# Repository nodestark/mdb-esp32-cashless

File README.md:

<div align="center">

# VMflow — Open-Source Vending Machine IoT Platform

**The first open-source vending platform designed for AI agents.**
</div>

---

The project aims to provide a modern, open, and extensible platform for vending machine connectivity. Based on the ESP32 platform, it enables machines to communicate via Bluetooth and cloud services, receive remote credits, report telemetry, and integrate with mobile applications and web dashboards.

# Features
- ESP32-based vending machine controller implementing MDB telemetry, cashless payments, and IoT connectivity;
- PCB design done in **KiCad**, facilitating production and customization of the hardware;
- Support for **EVA DTS DEX/DDCMP** (European Vending Association Data Transfer Standard), allowing remote monitoring and control of machines;
- **Web Dashboard**: [📊 Open Dashboard](https://vmflow.xyz/dashboard) – Centralized interface to monitor the vending machine network in real time, including device status, telemetry, sales data, inventory control, product catalog management, and real-time stock alerts. Features AI-powered diagnostics (via OpenAI) for operation-wide analysis, per-machine insights, and product catalog recommendations;
- **PAX Counter**: detects nearby mobile devices and periodically reports anonymized presence metrics to estimate foot traffic around the vending machine. This enables heatmaps, peak-hour analysis, and location performance insights;

# 🤖 Manage It With Your AI Agent

VMflow is built to be driven by AI agents — send credits, check device health, query sales, and trigger OTA updates, all from natural language.

**OpenClaw** — install the official VMflow skill:
```
$ openclaw skills install @nodestark/vmflow
```

**Any coding agent with a shell** (Claude Code, Codex, etc.) — [vmflow-cli](https://github.com/nodestark/vmflow-cli), browser login, no tokens to copy/paste:
```bash
npm install -g vmflow-cli
vmflow-cli auth login
vmflow-cli device credit 51 1.50   # everything else: vmflow-cli --help
```

**Agents without shell access** (ChatGPT, browser-based assistants) — paste this and it picks up the whole API surface:
```
read https://raw.githubusercontent.com/nodestark/mdb-esp32-cashless/main/AGENTS.md
```

# Getting Started

### 1. Flash the Firmware

👉 Install firmware via Web Installer (no setup required): **https://install.vmflow.xyz**

👉 Advanced (for development): ESP-IDF

```bash
# Clone the repository (with submodules — pulls in the VMC project)
git clone --recurse-submodules https://github.com/nodestark/mdb-esp32-cashless
cd mdb-esp32-cashless/mdb-slave-esp32s3

idf.py flash monitor
```
### 2. Register and Configure the Device — VMflow [Android App](./android)

Use the **VMflow Android app** to register the board and link it to your operator account. The app allows you to:

- **Device Registration**: register telemetry boards and bind them to your operator account
- **Wi-Fi Configuration**: remotely configure the Wi-Fi network of your devices via Bluetooth
- **Send Credits**: interact with devices in real time via Bluetooth and MQTT

## Hardware

---

### 1️⃣ Get a Bearer Token

```bash
curl -X POST 'https://supabase.vmflow.xyz/auth/v1/token?grant_type=password' \
-H "apikey: eyJhbGciOiJIUzI1NiIsInR5cCI6IkpXVCJ9.eyJyb2xlIjoiYW5vbiIsImlzcyI6InN1cGFiYXNlLWRlbW8iLCJpYXQiOjE2NDE3NjkyMDAsImV4cCI6MTc5OTUzNTYwMH0.VGEEIztVo-do9cy_Qw2-2sF8bSONckhX71Nvtwj15X4" \
-H "Content-Type: application/json" \
-d '{ "email": "your_email@domain.xyz", "password": "your_password"}'
```

### 2️⃣ Send Credit to the Machine over MQTT

```bash
curl -X POST 'https://supabase.vmflow.xyz/functions/v1/send-credit' \
-H "apikey: eyJhbGciOiJIUzI1NiIsInR5cCI6IkpXVCJ9.eyJyb2xlIjoiYW5vbiIsImlzcyI6InN1cGFiYXNlLWRlbW8iLCJpYXQiOjE2NDE3NjkyMDAsImV4cCI6MTc5OTUzNTYwMH0.VGEEIztVo-do9cy_Qw2-2sF8bSONckhX71Nvtwj15X4" \
-H "Authorization: Bearer YOUR_ACCESS_TOKEN" \
-H "Content-Type: application/json" \
-d '{ "subdomain":51,"amount":1.50 }'
```

### 💸 Pay with x402 (crypto / AI agents)

[x402](https://x402.org) lets a person or an AI agent pay a machine directly over HTTP — no checkout page, no webhook. Call without payment to get a 402 quote, retry with a signed `X-PAYMENT` header to vend. Operator setup: add a `credentials` row with key `x402_pay_to` and your receiving wallet address.

```bash
# 1. Get a quote (returns 402 + payment requirements)
curl -X POST 'https://supabase.vmflow.xyz/functions/v1/x402-vend' \
-H "apikey: eyJhbGciOiJIUzI1NiIsInR5cCI6IkpXVCJ9.eyJyb2xlIjoiYW5vbiIsImlzcyI6InN1cGFiYXNlLWRlbW8iLCJpYXQiOjE2NDE3NjkyMDAsImV4cCI6MTc5OTUzNTYwMH0.VGEEIztVo-do9cy_Qw2-2sF8bSONckhX71Nvtwj15X4" \
-H "Content-Type: application/json" \
-d '{ "subdomain":51,"amount":1.50 }'

# 2. Retry with the signed payment (any x402 client library builds this header)
curl -X POST 'https://supabase.vmflow.xyz/functions/v1/x402-vend' \
-H "apikey: eyJhbGciOiJIUzI1NiIsInR5cCI6IkpXVCJ9.eyJyb2xlIjoiYW5vbiIsImlzcyI6InN1cGFiYXNlLWRlbW8iLCJpYXQiOjE2NDE3NjkyMDAsImV4cCI6MTc5OTUzNTYwMH0.VGEEIztVo-do9cy_Qw2-2sF8bSONckhX71Nvtwj15X4" \
-H "X-PAYMENT: <base64 payment payload>" \
-H "Content-Type: application/json" \
-d '{ "subdomain":51,"amount":1.50 }'
```

**Operator payouts:** [vmflow-spraay](https://github.com/plagtech/vmflow-spraay) — automated multi-party revenue splits for VMflow sales, settled as one batch transaction on Base (non-custodial, MIT).

### 3️⃣ View Sales

```bash
curl -X GET 'https://supabase.vmflow.xyz/rest/v1/sales' \
-H "apikey: eyJhbGciOiJIUzI1NiIsInR5cCI6IkpXVCJ9.eyJyb2xlIjoiYW5vbiIsImlzcyI6InN1cGFiYXNlLWRlbW8iLCJpYXQiOjE2NDE3NjkyMDAsImV4cCI6MTc5OTUzNTYwMH0.VGEEIztVo-do9cy_Qw2-2sF8bSONckhX71Nvtwj15X4" \
-H "Authorization: Bearer YOUR_ACCESS_TOKEN"
```

### 4️⃣ View Devices

```bash
curl -X GET 'https://supabase.vmflow.xyz/rest/v1/embedded' \
-H "apikey: eyJhbGciOiJIUzI1NiIsInR5cCI6IkpXVCJ9.eyJyb2xlIjoiYW5vbiIsImlzcyI6InN1cGFiYXNlLWRlbW8iLCJpYXQiOjE2NDE3NjkyMDAsImV4cCI6MTc5OTUzNTYwMH0.VGEEIztVo-do9cy_Qw2-2sF8bSONckhX71Nvtwj15X4" \
-H "Authorization: Bearer YOUR_ACCESS_TOKEN"
```

### 5️⃣ View Paxcounter

```bash
curl -X GET 'https://supabase.vmflow.xyz/rest/v1/metrics?name=eq.paxcounter' \
-H "apikey: eyJhbGciOiJIUzI1NiIsInR5cCI6IkpXVCJ9.eyJyb2xlIjoiYW5vbiIsImlzcyI6InN1cGFiYXNlLWRlbW8iLCJpYXQiOjE2NDE3NjkyMDAsImV4cCI6MTc5OTUzNTYwMH0.VGEEIztVo-do9cy_Qw2-2sF8bSONckhX71Nvtwj15X4" \
-H "Authorization: Bearer YOUR_ACCESS_TOKEN"
```

# How to Contribute:
- Contributions are welcome! Feel free to open issues, send pull requests, or propose new features
- Before submitting a pull request, make sure the code complies with the style and quality guidelines defined in the project
- Help us improve documentation by adding usage examples, installation instructions, and any other relevant information

## License

This project is licensed under the MIT License - see the [LICENSE](LICENSE) file for details.

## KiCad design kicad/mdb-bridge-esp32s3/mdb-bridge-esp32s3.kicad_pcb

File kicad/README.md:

# MDB ESP32 Cashless Devices

This repository contains open hardware projects for MDB-based cashless devices built around the ESP32 platform.

## PCBWay Project Store
You can view and order the PCBs directly from PCBWay using the link below:

👉 https://www.pcbway.com/project/member/?bmbno=1B3B95CB-4E28-4D

---

### MDB ESP32 Cashless Device

[Schematic (PDF)](schematic-mdb-slave-esp32s3.pdf)

### MDB ESP32 GPS/LTE-M/NB-IoT Cashless Device

[Schematic (PDF)](schematic-mdb-slave-esp32s3-sim7080g.pdf)

### MDB ESP32 Cashless Device (Mini, 0402)

[Schematic (PDF)](schematic-mdb-slave-esp32s3-mini.pdf)

### MDB ESP32 Cashless/VMC Device

[Schematic (PDF)](schematic-mdb-bridge-esp32s3.pdf)

Two independent MDB ports: the board is the master on the **controller** port (peripherals: coin changer, bill validator) and a slave on the **target** port (the vending machine's VMC).

| Port           | RX  | TX  | Board role         | Connects to                               |
|----------------|-----|-----|--------------------|-------------------------------------------|
| **Controller** | IO1 | IO2 | master (VMC)       | peripherals: coin changer, bill validator |
| **Target**     | IO4 | IO5 | slave (peripheral) | the vending machine's VMC/master          |

### MDB ESP32 AI Bridge (VMflow + VMC + Bill/Coin Reader simulator)
Three ESP32-S3 on one board, each simulating one role of the vending stack — VMflow cashless device, VMC and bill/coin reader — linked by logic-level MDB and reachable through a single USB-C via a USB2514B hub. Bench/CI target for firmware and AI agents without a vending machine.

[Schematic (PDF)](schematic-mdb-ai-bridge-esp32s3.pdf)

The bridge MCU keeps the pinout of the MDB ESP32 Cashless/VMC Device, so the same firmware runs on both boards; the two simulators sit on its ports in place of the real peripherals and VMC.

| MCU    | Role                               | MDB RX | MDB TX | USB hub port |
|--------|------------------------------------|--------|--------|--------------|
| **U5** | VMflow bridge, controller port     | IO1    | IO2    | 2            |
| **U5** | VMflow bridge, target port         | IO4    | IO5    | 2            |
| **U2** | bill/coin reader simulator (slave) | IO4    | IO5    | 1            |
| **U1** | VMC simulator (master)             | IO1    | IO2    | 3            |

The bridge also reaches the VMC simulator's UART0 console (bridge IO8 ← U0TXD, IO9 → U0RXD). I²C (SDA IO10, SCL IO11) is shared by all three, with 4.7k pull-ups. The J3 2×8 header exposes both MDB links, the I²C bus and bridge IO12–IO14, IO17 and IO18.

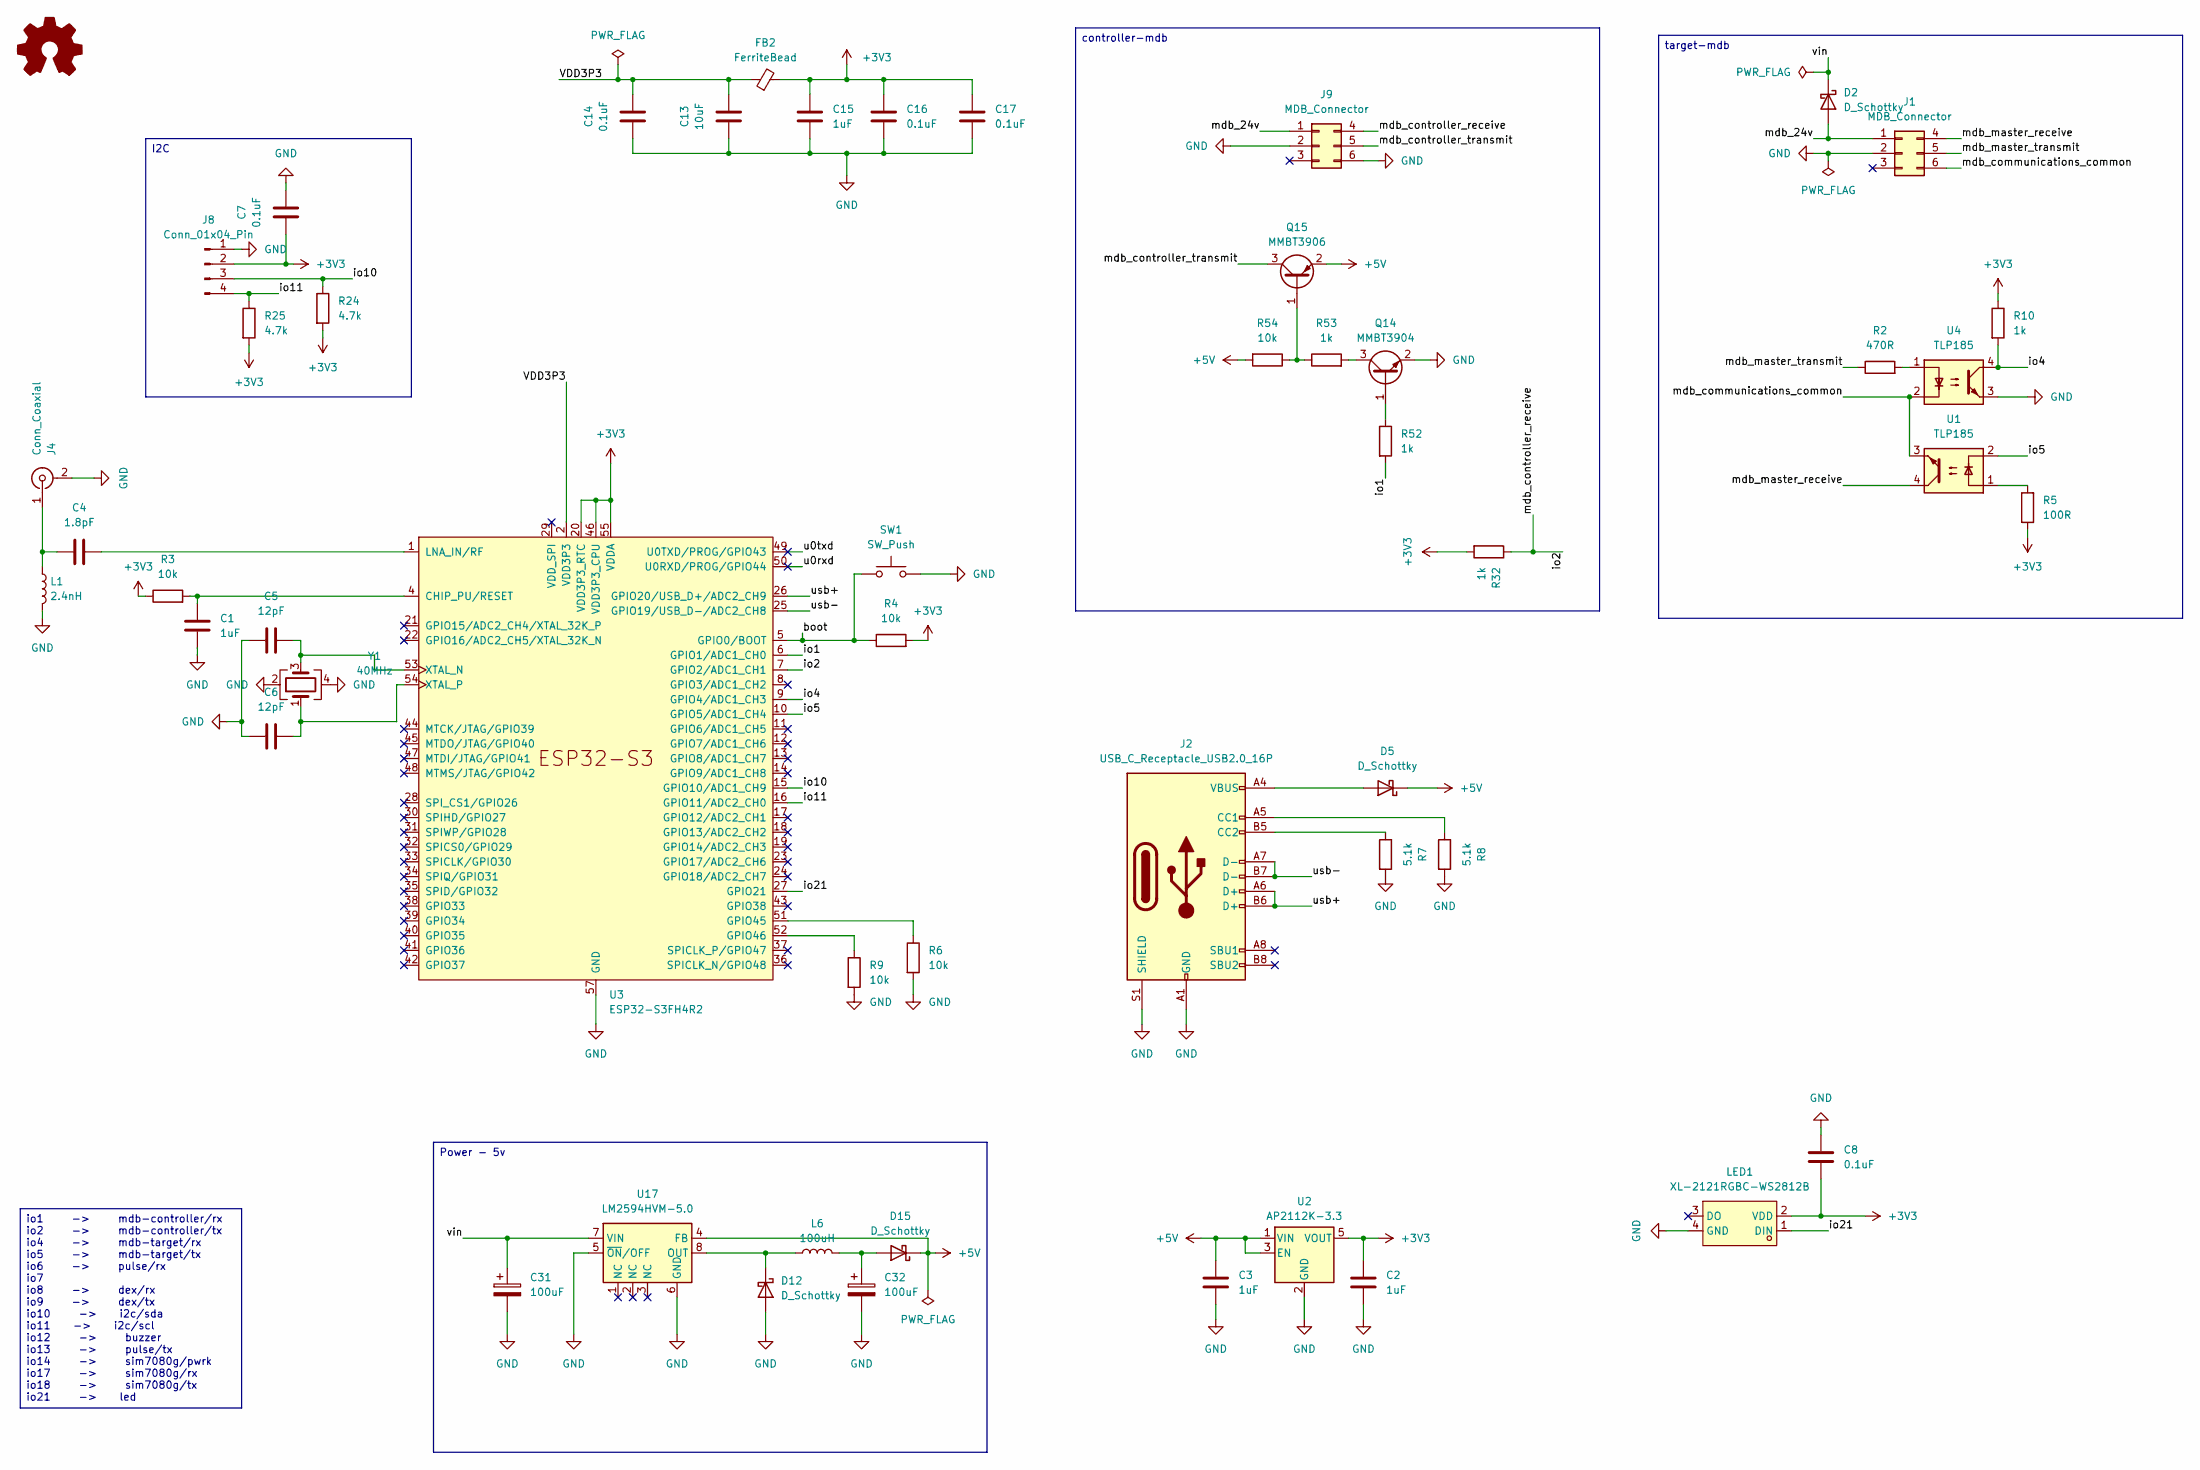
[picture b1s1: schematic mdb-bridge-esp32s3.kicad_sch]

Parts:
C1, C2, C3, C15: 1uF; C_0603_1608Metric; LCSC# C696901
C4: 1.8pF; C_0603_1608Metric; LCSC# C376773
C5, C6: 12pF; C_0603_1608Metric; LCSC# C363546
C7, C8, C14, C16, C17: 0.1uF; C_0603_1608Metric; LCSC# C5137636
C13: 10uF; C_0603_1608Metric; LCSC# C6119864
C31: 100uF; CP_Elec_6.3x5.8; LCSC# C128464
C32: 100uF; CP_EIA-3528-21_Kemet-B; LCSC# C90975
D2, D5, D12, D15: D_Schottky; D_SOD-123; LCSC# C18195164
FB2: FerriteBead; L_0603_1608Metric; LCSC# C14709
J1, J9: MDB_Connector; Molex_Mini-Fit_Jr_5566-06A_2x03_P4.20mm_Vertical; LCSC# C22365701
J2: USB_C_Receptacle_USB2.0_16P; USB_C_Receptacle_G-Switch_GT-USB-7010ASV; LCSC# C2988369
J4: Conn_Coaxial; U.FL_Hirose_U.FL-R-SMT-1_Vertical; LCSC# C88374
J8: Conn_01x04_Pin; JST_PH_B4B-PH-K_1x04_P2.00mm_Vertical; LCSC# C131334
L1: 2.4nH; L_0603_1608Metric; LCSC# C2042508
L6: 100uH; L_7.3x7.3_H3.5; LCSC# C182195
LED1: XL-2121RGBC-WS2812B; LED-SMD_4P-L2.1-W2.1-BR_XL-2121RGBC-WS2812B; MPN XL-2121RGBC-2812B; LCSC# C5349957
Q14: MMBT3904; SOT-23; LCSC# C916374
Q15: MMBT3906; SOT-23; LCSC# C364311
R2: 470R; R_0603_1608Metric; LCSC# C114669
R3, R4, R6, R9, R54: 10k; R_0603_1608Metric; LCSC# C98220
R5: 100R; R_0603_1608Metric; LCSC# C22775
R7, R8: 5.1k; R_0603_1608Metric; LCSC# C394543
R10, R32, R52, R53: 1k; R_0603_1608Metric; LCSC# C2907113
R24, R25: 4.7k; R_0603_1608Metric; LCSC# C23162
SW1: SW_Push; SW_Tactile_SPST_NO_Straight_CK_PTS636Sx25SMTRLFS; LCSC# C42435421
U1, U4: TLP185; SOP-4_3.8x4.1mm_P2.54mm; LCSC# C128776
U2: AP2112K-3.3; SOT-23-5; LCSC# C51118
U3: ESP32-S3FH4R2; QFN-56-1EP_7x7mm_P0.4mm_EP4x4mm; LCSC# C3013940
U17: LM2594HVM-5.0; SOIC-8_3.9x4.9mm_P1.27mm; LCSC# C2904794
Y1: 40MHz; Crystal_SMD_3225-4Pin_3.2x2.5mm; LCSC# C7294599

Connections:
+3V3: C2.2, C7.1, C8.2, C15.2, C16.1, C17.1, FB2.2, J8.2, LED1.2 (VDD), R3.1, R4.2, R5.1, R10.1, R24.2, R25.2, R32.2, U2.5 (VOUT), U3.20 (VDD3P3_RTC), U3.46 (VDD3P3_CPU), U3.55 (VDDA), U3.56 (VDDA)
+5V: C3.2, D5.1 (K), D15.1 (K), Q15.2 (E), R54.2, U2.1 (VIN), U2.3 (EN), U17.4 (FB)
/boot: R4.1, SW1.1, U3.5 (GPIO0/BOOT)
/io1: R52.2, U3.6 (GPIO1/ADC1_CH0)
/io2: J9.4, R32.1, U3.7 (GPIO2/ADC1_CH1)
/io4: R10.2, U3.9 (GPIO4/ADC1_CH3), U4.4
/io5: U1.2, U3.10 (GPIO5/ADC1_CH4)
/io10: J8.3, R24.1, U3.15 (GPIO10/ADC1_CH9)
/io11: J8.4, R25.1, U3.16 (GPIO11/ADC2_CH0)
/io21: LED1.1 (DIN), U3.27 (GPIO21)
/mdb_24v: D2.2 (A), J1.1, J9.1
/mdb_communications_common: J1.6, U1.3, U4.2
/mdb_controller_transmit: J9.5, Q15.3 (C)
/mdb_master_receive: J1.4, U1.4
/mdb_master_transmit: J1.5, R2.1
/u0rxd: U3.50 (U0RXD/PROG/GPIO44)
/u0txd: U3.49 (U0TXD/PROG/GPIO43)
/usb+: J2.A6 (D+), J2.B6 (D+), U3.26 (GPIO20/USB_D+/ADC2_CH9)
/usb-: J2.A7 (D-), J2.B7 (D-), U3.25 (GPIO19/USB_D-/ADC2_CH8)
/vin: C31.1, D2.1 (K), U17.7 (VIN)
GND: C1.2, C2.1, C3.1, C5.1, C6.1, C7.2, C8.1, C13.1, C14.1, C15.1, C16.2, C17.2, C31.2, C32.2, D12.2 (A), J1.2, J2.A1 (GND), J2.A12 (GND), J2.B1 (GND), J2.B12 (GND), J2.S1 (SHIELD), J4.2 (Ext), J8.1, J9.2, J9.6, L1.2, LED1.4 (GND), Q14.2 (E), R6.2, R7.2, R8.2, R9.2, SW1.2, U2.2 (GND), U3.57 (GND), U4.3, U17.5 (~ON/OFF), U17.6 (GND), Y1.2, Y1.4
unnamed: D5.2 (A), J2.A4 (VBUS), J2.A9 (VBUS), J2.B4 (VBUS), J2.B9 (VBUS)
unnamed: D12.1 (K), L6.1, U17.8 (OUT)
unnamed: C32.1, D15.2 (A), L6.2
unnamed: J2.A5 (CC1), R8.1
unnamed: J2.B5 (CC2), R7.1
unnamed: C4.1, J4.1 (In), L1.1
unnamed: Q14.1 (B), R52.1
unnamed: Q14.3 (C), R53.2
unnamed: Q15.1 (B), R53.1, R54.1
unnamed: R2.2, U4.1
unnamed: R5.2, U1.1
unnamed: C1.1, R3.2, U3.4 (CHIP_PU/RESET)
unnamed: R6.1, U3.51 (GPIO45)
unnamed: R9.1, U3.52 (GPIO46)
unnamed: C4.2, U3.1 (LNA_IN/RF)
unnamed: C5.2, U3.53 (XTAL_N), Y1.3
unnamed: C6.2, U3.54 (XTAL_P), Y1.1
VDD3P3: C13.2, C14.2, FB2.1, U3.2 (VDD3P3), U3.3 (VDD3P3)

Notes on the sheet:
io1 -> mdb-controller/rx io2 -> mdb-controller/tx io4 -> mdb-target/rx io5 -> mdb-target/tx io6 -> pulse/rx io7 io8 -> dex/rx io9 -> dex/tx io10 -> i2c/sda io11 -> i2c/scl io12 -> buzzer io13 -> pulse/tx io14 -> sim7080g/pwrk io17 -> sim7080g/rx io18 -> sim7080g/tx io21 -> led
controller-mdb
Power - 5v
target-mdb
I2C

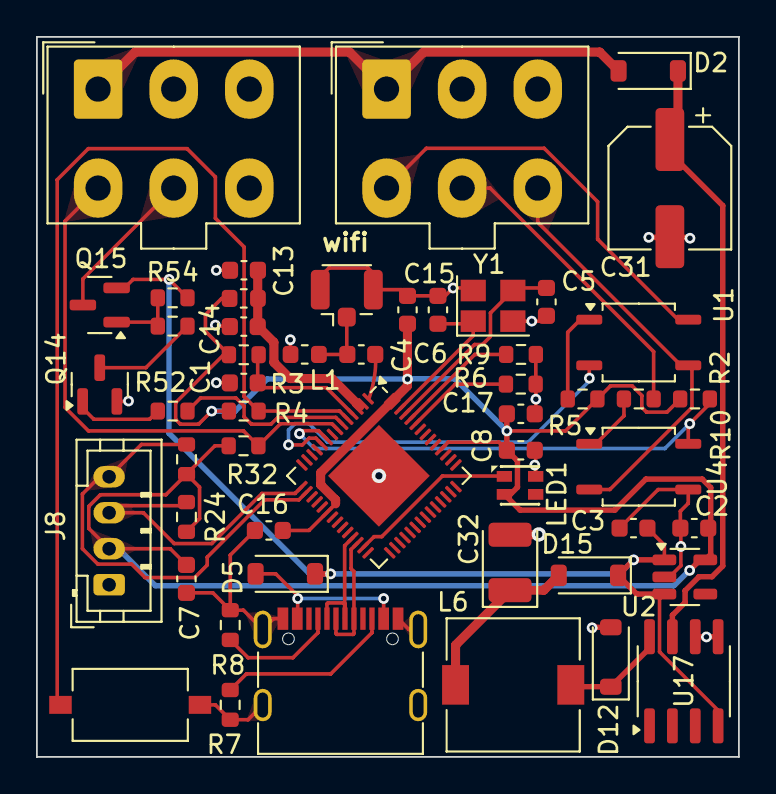
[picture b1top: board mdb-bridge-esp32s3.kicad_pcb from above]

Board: 2 copper layers, 39.0 x 40.0 mm, 52 parts (0 on the bottom side), 37 nets.

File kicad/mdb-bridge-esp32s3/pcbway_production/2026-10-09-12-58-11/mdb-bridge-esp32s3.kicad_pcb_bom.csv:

Designator,Quantity,Value,Footprint,Package,MPN,DNP,Mount_Type,LCSC#,Description,Manufacturer,Sim.Device,Sim.Pins
"C1, C15, C2, C3",4,1uF,C_0603_1608Metric,,,,smt,C696901,,,,
C13,1,10uF,C_0603_1608Metric,,,,smt,C6119864,,,,
"C14, C16, C17, C7, C8",5,0.1uF,C_0603_1608Metric,,,,smt,C5137636,,,,
C31,1,100uF,CP_Elec_6.3x5.8,,,,smt,C128464,Polarized capacitor,,,
C32,1,100uF,CP_EIA-3528-21_Kemet-B,,,,smt,C90975,Polarized capacitor,,,
C4,1,1.8pF,C_0603_1608Metric,,,,smt,C376773,,,,
"C5, C6",2,12pF,C_0603_1608Metric,,,,smt,C363546,,,,
"D12, D15, D2, D5",4,D_Schottky,D_SOD-123,,,,smt,C18195164,Schottky diode,,,
FB2,1,FerriteBead,L_0603_1608Metric,,,,smt,C14709,"Ferrite bead, small symbol",,,
"J1, J9",2,MDB_Connector,Molex_Mini-Fit_Jr_5566-06A_2x03_P4.20mm_Vertical,,,,tht,C22365701,"Generic connector, double row, 02x03, top/bottom pin numbering scheme (row 1: 1...pins_per_row, row2: pins_per_row+1 ... num_pins), script generated (kicad-library-utils/schlib/autogen/connector/)",,,
J2,1,USB_C_Receptacle_USB2.0_16P,USB_C_Receptacle_G-Switch_GT-USB-7010ASV,,,,smt,C2988369,USB 2.0-only 16P Type-C Receptacle connector,,,
J4,1,Conn_Coaxial,U.FL_Hirose_U.FL-R-SMT-1_Vertical,,,,smt,C88374,"coaxial connector (BNC, SMA, SMB, SMC, Cinch/RCA, LEMO, ...)",,,
J8,1,Conn_01x04_Pin,JST_PH_B4B-PH-K_1x04_P2.00mm_Vertical,,,,tht,C131334,"Generic connector, single row, 01x04, script generated",,,
L1,1,2.4nH,L_0603_1608Metric,,,,smt,C2042508,,,,
L6,1,100uH,L_7.3x7.3_H3.5,,,,smt,C182195,Inductor,,,
LED1,1,XL-2121RGBC-WS2812B,LED-SMD_4P-L2.1-W2.1-BR_XL-2121RGBC-WS2812B,,XL-2121RGBC-2812B,,smt,C5349957,,XINGLIGHT(成兴光),,
Q5,1,MMBT3906,SOT-23,,,,smt,C364311,"-0.2A Ic, -40V Vce, Small Signal PNP Transistor, SOT-23",,PNP,1=B 2=E 3=C
"R1, R10, R32",3,1k,R_0603_1608Metric,,,,smt,C2907113,,,,
R2,1,470R,R_0603_1608Metric,,,,smt,C114669,Resistor,,,
R5,1,100R,R_0603_1608Metric,,,,smt,C22775,Resistor,,,
"R24, R25, R31",3,4.7k,R_0603_1608Metric,,,,smt,C23162,,,,
"R3, R4, R6, R9",4,10k,R_0603_1608Metric,,,,smt,C98220,,,,
"R7, R8",2,5.1k,R_0603_1608Metric,,,,smt,C394543,,,,
SW1,1,SW_Push,SW_Tactile_SPST_NO_Straight_CK_PTS636Sx25SMTRLFS,,,,smt,C42435421,,,,
"U1, U4",2,TLP785,SOP-4_3.8x4.1mm_P2.54mm,,,,smt,C128776,"DC Optocoupler, Vce 80V, CTR 50-200%, DIP4",,,
U17,1,LM2594HVM-5.0,SOIC-8_3.9x4.9mm_P1.27mm,,,,smt,C2904794,"5.0V, 0.5A SIMPLE SWITCHER® Step-Down Voltage Regulator, Maximum VIN 60V, SOIC-8",,,
U2,1,AP2112K-3.3,SOT-23-5,,,,smt,C51118,"600mA low dropout linear regulator, with enable pin, 3.8V-6V input voltage range, 3.3V fixed positive output, SOT-23-5",,,
U3,1,ESP32-S3FH4R2,QFN-56-1EP_7x7mm_P0.4mm_EP4x4mm,,,,smt,C3013940,,,,
Y1,1,40MHz,Crystal_SMD_3225-4Pin_3.2x2.5mm,,,,smt,C7294599,"Four pin crystal, GND on pins 2 and 4",,,

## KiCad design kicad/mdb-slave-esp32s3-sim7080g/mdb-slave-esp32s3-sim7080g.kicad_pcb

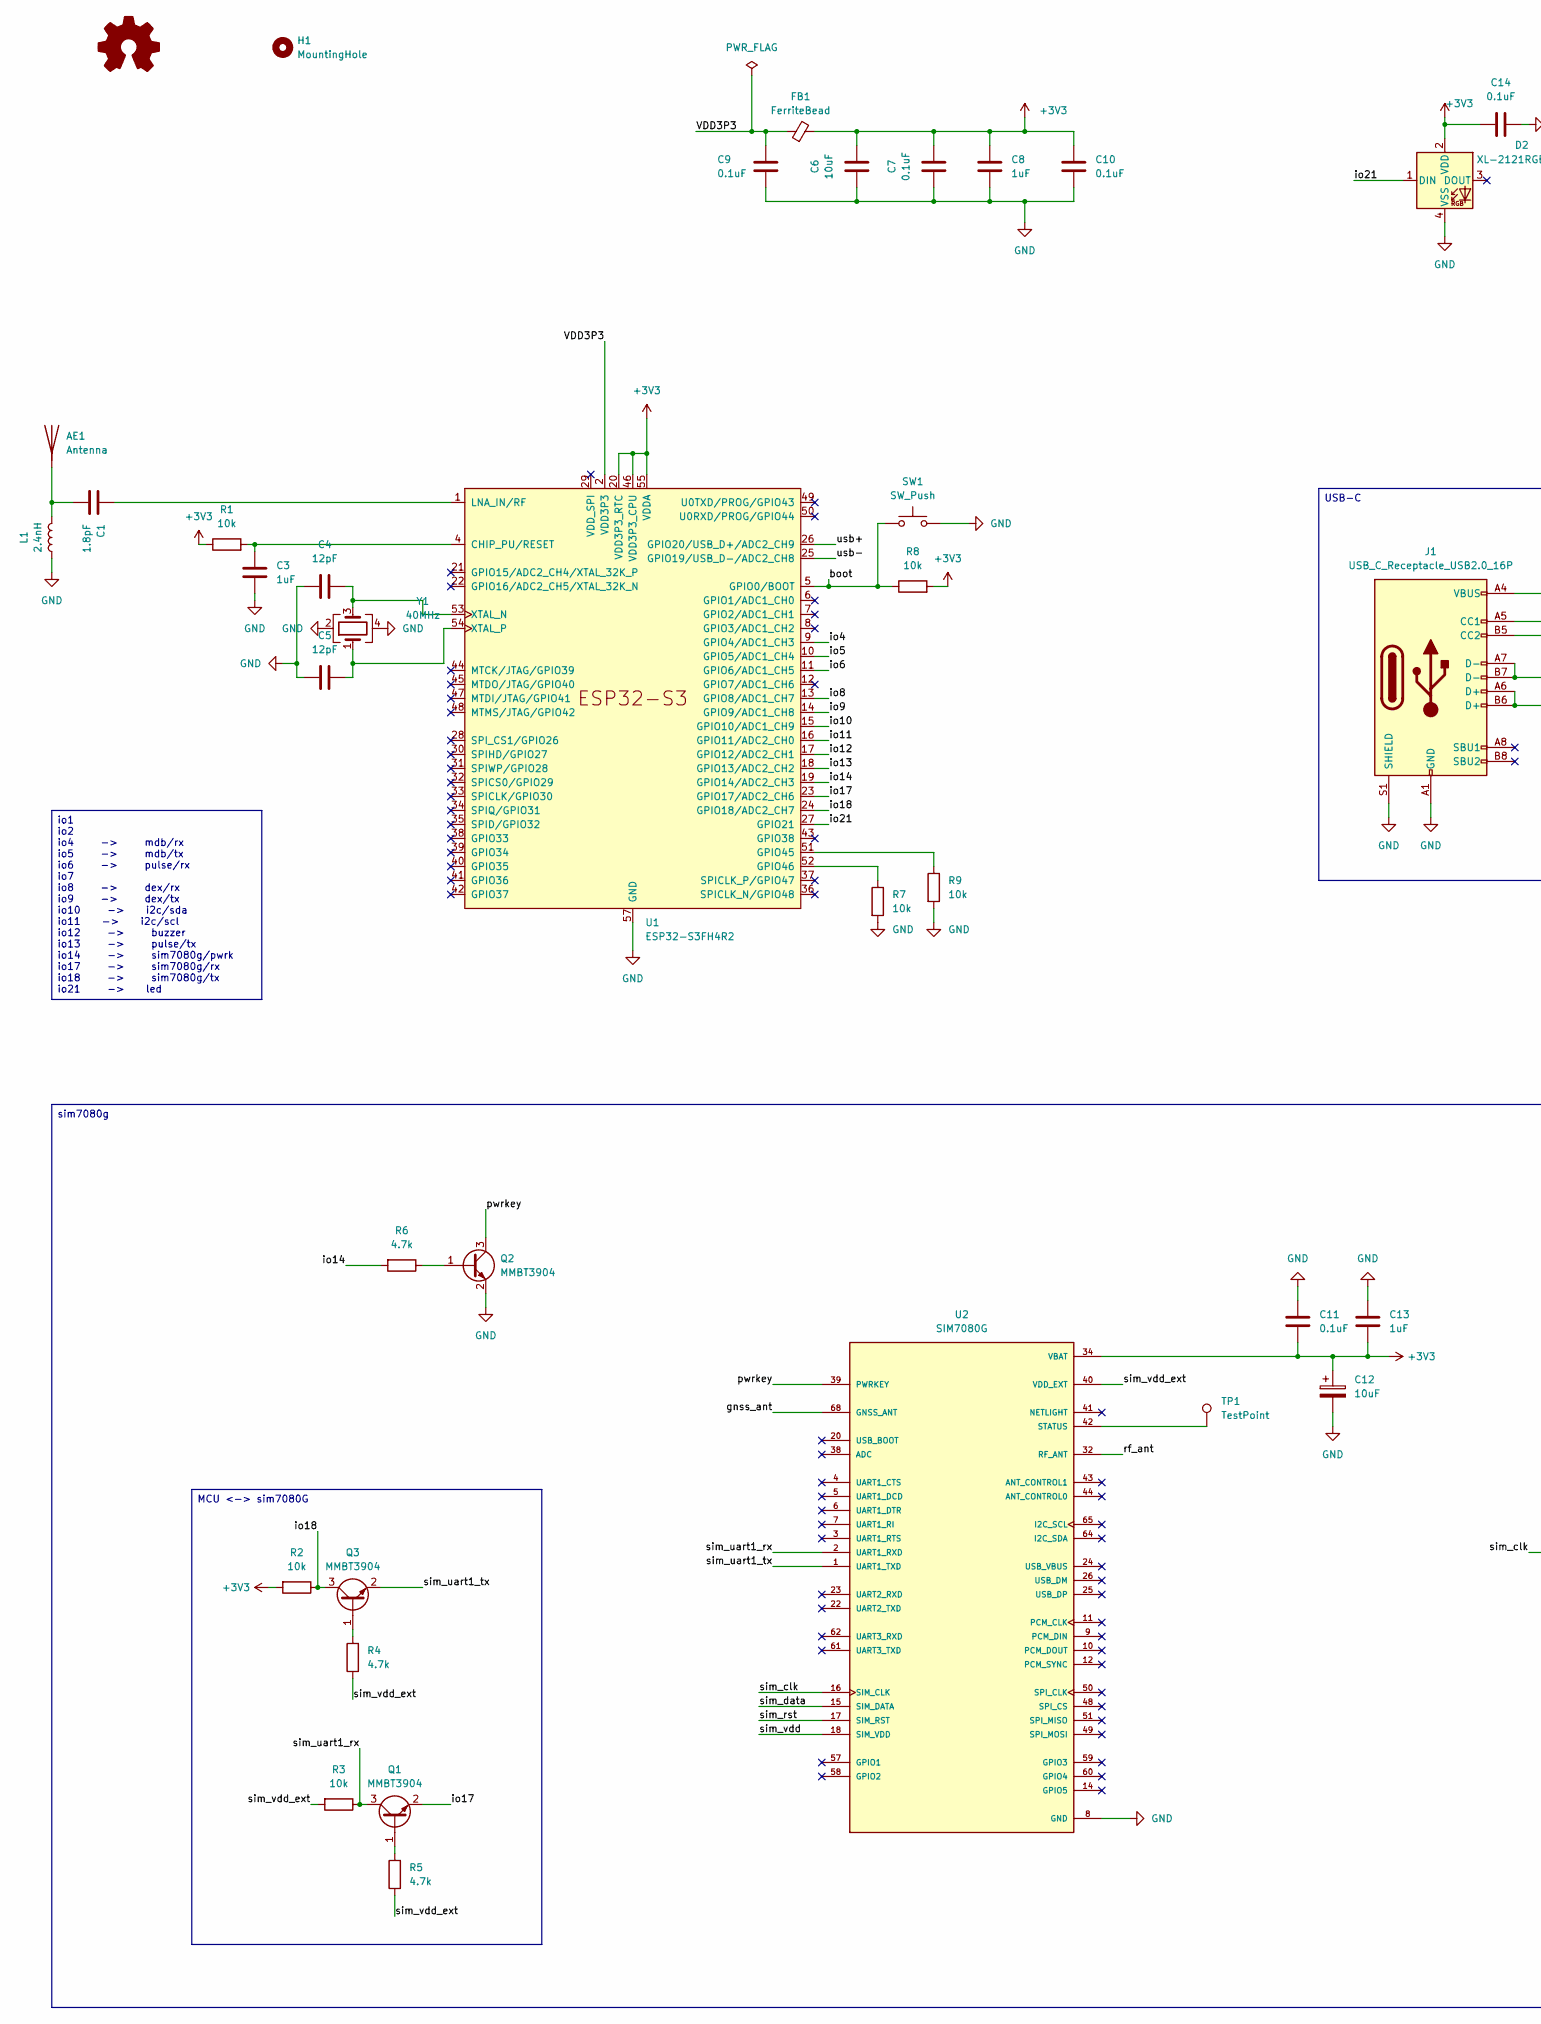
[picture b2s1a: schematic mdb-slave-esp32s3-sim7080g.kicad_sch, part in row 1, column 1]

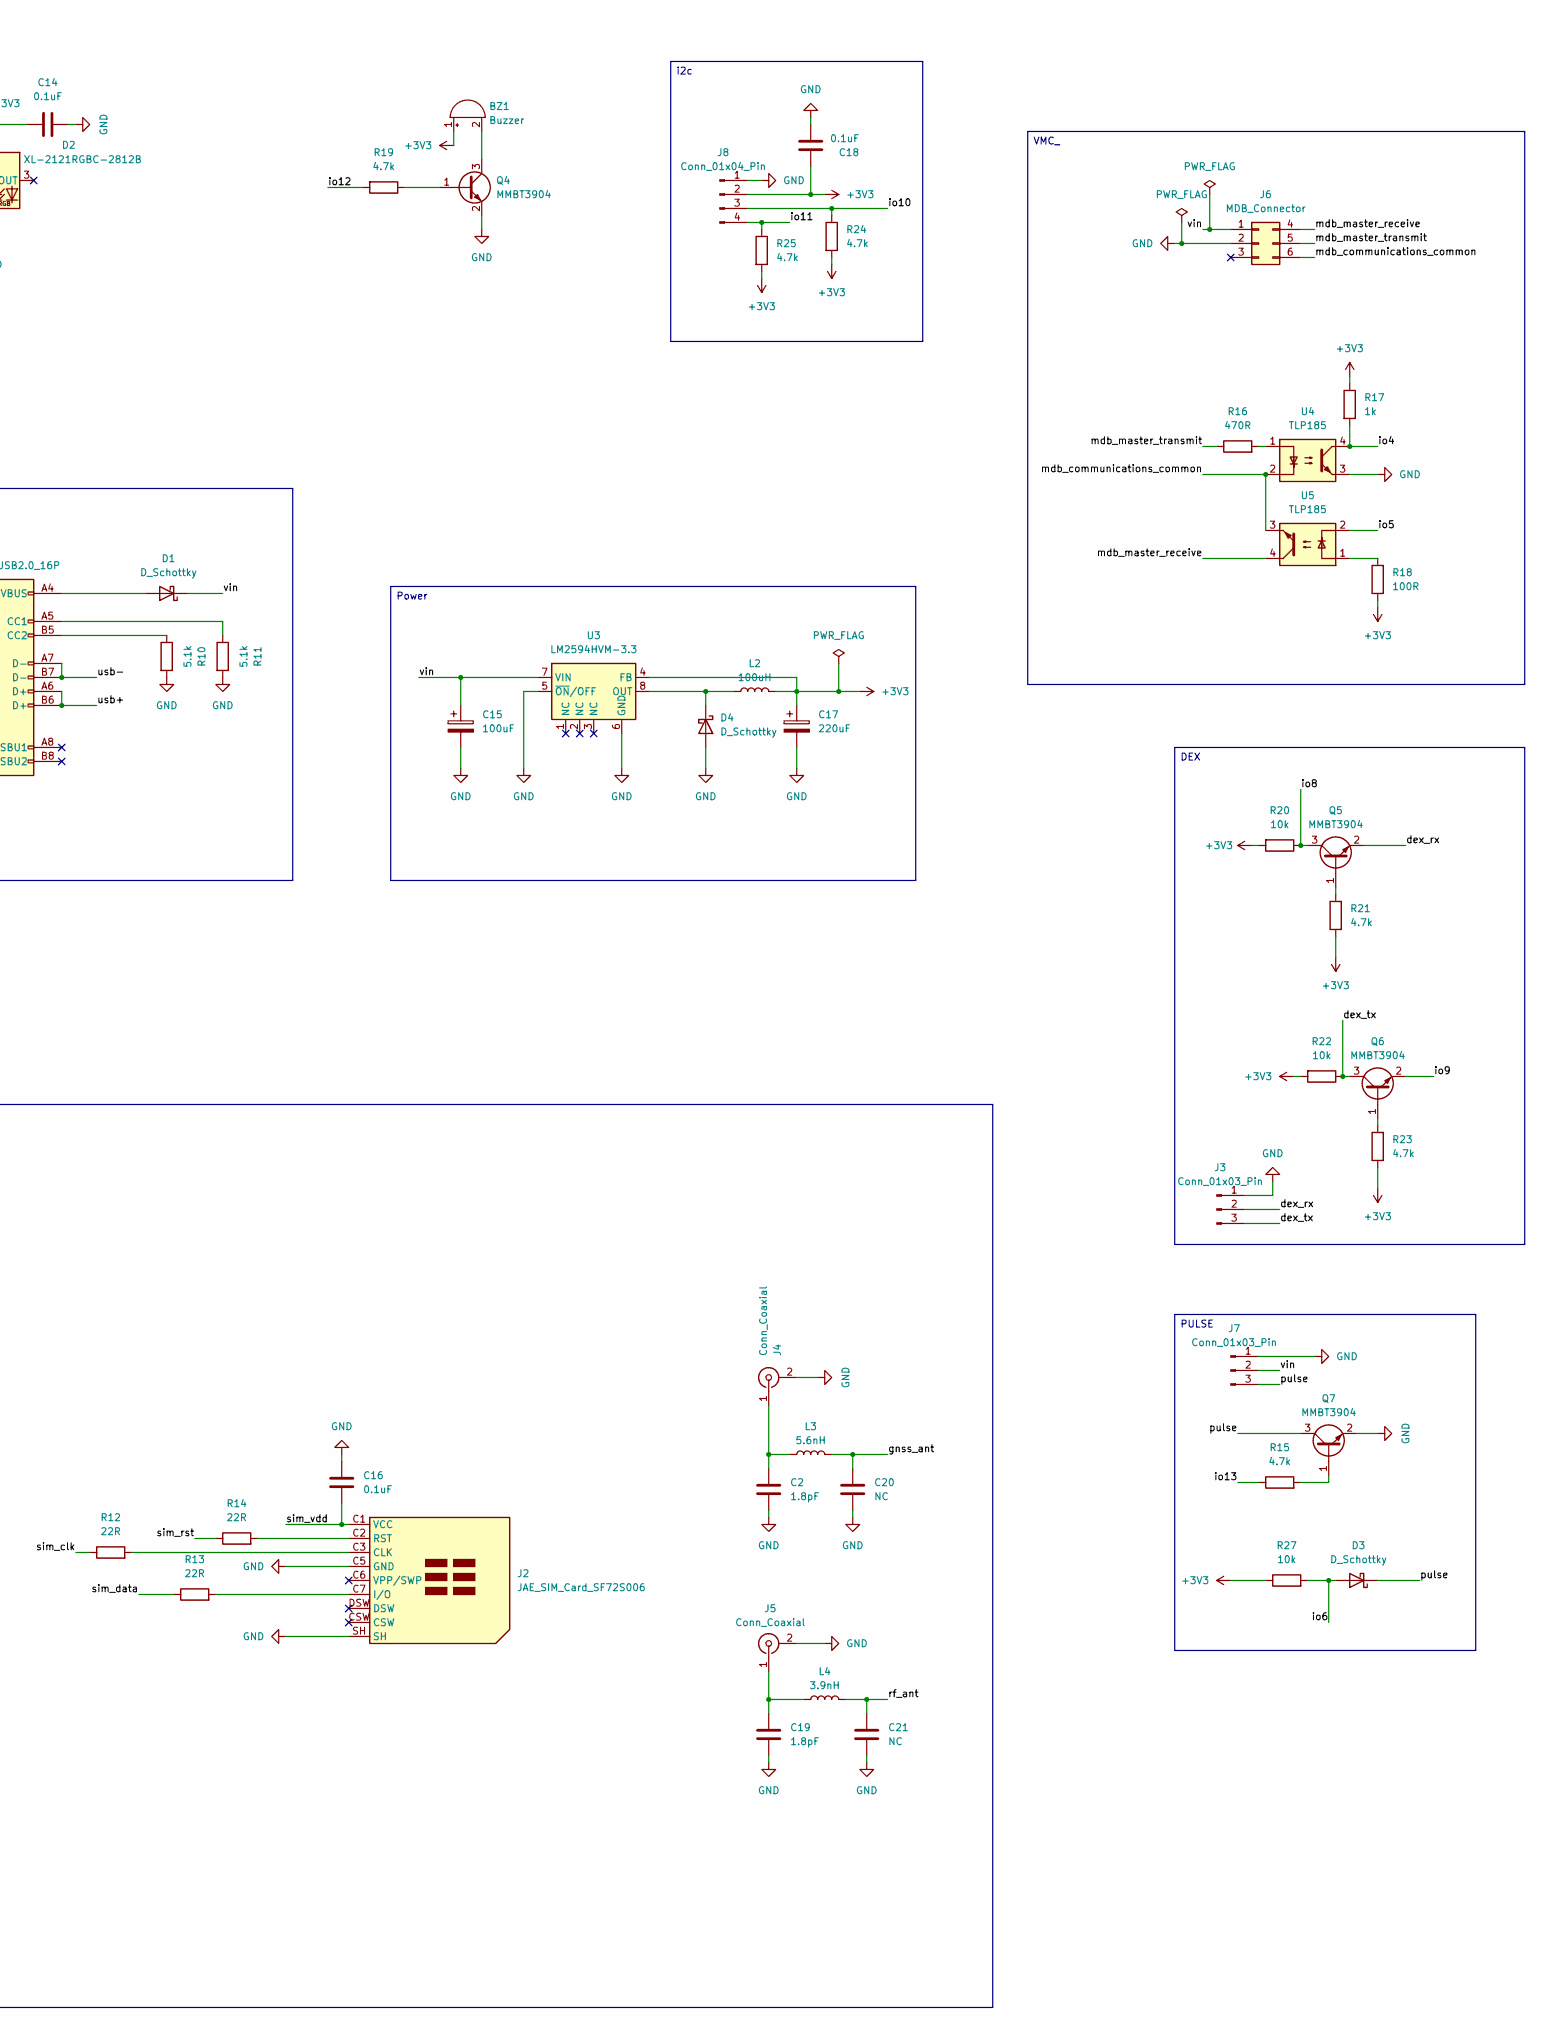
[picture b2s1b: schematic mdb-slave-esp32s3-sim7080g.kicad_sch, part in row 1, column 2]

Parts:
AE1: Antenna; Texas_SWRA117D_2.4GHz_Left
BZ1: Buzzer; Buzzer_CUI_CPT-9019S-SMT; LCSC# C255327
C1, C2, C19: 1.8pF; C_0603_1608Metric; LCSC# C376773
C3, C8, C13: 1uF; C_0603_1608Metric; LCSC# C6119849
C4, C5: 12pF; C_0603_1608Metric; LCSC# C363546
C6: 10uF; C_0603_1608Metric; LCSC# C6119864
C7, C9, C10, C11, C14, C16, C18: 0.1uF; C_0603_1608Metric; LCSC# C5137636
C12: 10uF; CP_EIA-3528-21_Kemet-B; LCSC# C110053
C15: 100uF; CP_Elec_6.3x5.8; LCSC# C128464
C17: 220uF; CP_EIA-3528-21_Kemet-B; LCSC# C30242
C20: NC; C_0603_1608Metric; LCSC# C376773
C21: NC; C_0603_1608Metric
D1, D3, D4: D_Schottky; D_SOD-123; LCSC# C18195164
D2: XL-2121RGBC-2812B; LED_WS2812B-2020_PLCC4_2.0x2.0mm; LCSC# C5349957
FB1: FerriteBead; L_0603_1608Metric; LCSC# C14709
H1: MountingHole; MountingHole_2.1mm
J1: USB_C_Receptacle_USB2.0_16P; USB_C_Receptacle_G-Switch_GT-USB-7010ASV; LCSC# C2988369
J2: JAE_SIM_Card_SF72S006; LCSC# C2977286
J3, J7: Conn_01x03_Pin; JST_PH_B3B-PH-K_1x03_P2.00mm_Vertical; LCSC# C131339
J4, J5: Conn_Coaxial; U.FL_Hirose_U.FL-R-SMT-1_Vertical; LCSC# C88374
J6: MDB_Connector; Molex_Mini-Fit_Jr_5566-06A_2x03_P4.20mm_Vertical; LCSC# C22365701
J8: Conn_01x04_Pin; JST_PH_B4B-PH-K_1x04_P2.00mm_Vertical; LCSC# C131334
L1: 2.4nH; L_0603_1608Metric; LCSC# C2042508
L2: 100uH; L_7.3x7.3_H3.5; LCSC# C182195
L3: 5.6nH; L_0603_1608Metric; LCSC# C6652920
L4: 3.9nH; L_0603_1608Metric; LCSC# C317982
Q1, Q2, Q3, Q4, Q5, Q6, Q7: MMBT3904; SOT-23; LCSC# C916374
R1, R2, R3, R7, R8, R9, R20, R22, R27: 10k; R_0603_1608Metric; LCSC# C98220
R4, R5, R6, R15, R19, R21, R23, R24, R25: 4.7k; R_0603_1608Metric; LCSC# C23162
R10, R11: 5.1k; R_0603_1608Metric; LCSC# C394543
R12, R13, R14: 22R; R_0603_1608Metric; LCSC# C23345
R16: 470R; R_0603_1608Metric; LCSC# C114669
R17: 1k; R_0603_1608Metric; LCSC# C2907113
R18: 100R; R_0603_1608Metric; LCSC# C22775
SW1: SW_Push; SW_Tactile_SPST_NO_Straight_CK_PTS636Sx25SMTRLFS; LCSC# C42435421
TP1: TestPoint; TestPoint_Pad_D1.0mm
U1: ESP32-S3FH4R2; QFN-56-1EP_7x7mm_P0.4mm_EP4x4mm; LCSC# C3013940
U2: SIM7080G; XCVR_SIM7080G; PARTREV 1.04; LCSC# C2943992
U3: LM2594HVM-3.3; SOIC-8_3.9x4.9mm_P1.27mm; LCSC# C18057294
U4, U5: TLP185; SOP-4_3.8x4.1mm_P2.54mm; LCSC# C128776
Y1: 40MHz; Crystal_SMD_3225-4Pin_3.2x2.5mm; LCSC# C7294599

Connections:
+3V3: BZ1.1 (+), C6.2, C7.2, C8.2, C10.1, C11.1, C12.1, C13.1, C14.2, C17.1, C18.1, D2.2 (VDD), FB1.2, J8.2, L2.2, R1.1, R2.2, R8.2, R17.1, R18.1, R20.2, R21.1, R22.2, R23.1, R24.2, R25.2, R27.1, U1.20 (VDD3P3_RTC), U1.46 (VDD3P3_CPU), U1.55 (VDDA), U1.56 (VDDA), U2.34 (VBAT), U2.35 (VBAT), U3.4 (FB)
/boot: R8.1, SW1.1, U1.5 (GPIO0/BOOT)
/dex_rx: J3.2, Q5.2 (E)
/dex_tx: J3.3, Q6.3 (C), R22.1
/gnss_ant: C20.2, L3.2, U2.68 (GNSS_ANT)
/io1: U1.6 (GPIO1/ADC1_CH0)
/io2: U1.7 (GPIO2/ADC1_CH1)
/io4: R17.2, U1.9 (GPIO4/ADC1_CH3), U4.4
/io5: U1.10 (GPIO5/ADC1_CH4), U5.2
/io6: D3.2 (A), R27.2, U1.11 (GPIO6/ADC1_CH5)
/io7: U1.12 (GPIO7/ADC1_CH6)
/io8: Q5.3 (C), R20.1, U1.13 (GPIO8/ADC1_CH7)
/io9: Q6.2 (E), U1.14 (GPIO9/ADC1_CH8)
/io10: J8.3, R24.1, U1.15 (GPIO10/ADC1_CH9)
/io11: J8.4, R25.1, U1.16 (GPIO11/ADC2_CH0)
/io12: R19.2, U1.17 (GPIO12/ADC2_CH1)
/io13: R15.1, U1.18 (GPIO13/ADC2_CH2)
/io14: R6.2, U1.19 (GPIO14/ADC2_CH3)
/io17: Q1.2 (E), U1.23 (GPIO17/ADC2_CH6)
/io18: Q3.3 (C), R2.1, U1.24 (GPIO18/ADC2_CH7)
/io21: D2.1 (DIN), U1.27 (GPIO21)
/mdb_communications_common: J6.6, U4.2, U5.3
/mdb_master_receive: J6.4, U5.4
/mdb_master_transmit: J6.5, R16.1
/netlight: U2.41 (NETLIGHT)
/pulse: D3.1 (K), J7.3, Q7.3 (C)
/pwrkey: Q2.3 (C), U2.39 (PWRKEY)
/rf_ant: C21.2, L4.2, U2.32 (RF_ANT)
/sim_clk: R12.1, U2.16 (SIM_CLK)
/sim_data: R13.1, U2.15 (SIM_DATA)
/sim_rst: R14.1, U2.17 (SIM_RST)
/sim_uart1_rx: Q1.3 (C), R3.1, U2.2 (UART1_RXD)
/sim_uart1_tx: Q3.2 (E), U2.1 (UART1_TXD)
/sim_vdd: C16.1, J2.C1 (VCC), U2.18 (SIM_VDD)
/sim_vdd_ext: R3.2, R4.1, R5.1, U2.40 (VDD_EXT)
/u0rxd: U1.50 (U0RXD/PROG/GPIO44)
/u0txd: U1.49 (U0TXD/PROG/GPIO43)
/usb+: J1.A6 (D+), J1.B6 (D+), U1.26 (GPIO20/USB_D+/ADC2_CH9)
/usb-: J1.A7 (D-), J1.B7 (D-), U1.25 (GPIO19/USB_D-/ADC2_CH8)
/vin: C15.1, D1.1 (K), J6.1, J7.2, U3.7 (VIN)
GND: C2.1, C3.2, C4.1, C5.1, C6.1, C7.1, C8.1, C9.2, C10.2, C11.2, C12.2, C13.2, C14.1, C15.2, C16.2, C17.2, C18.2, C19.1, C20.1, C21.1, D2.4 (VSS), D4.2 (A), J1.A1 (GND), J1.A12 (GND), J1.B1 (GND), J1.B12 (GND), J1.S1 (SHIELD), J2.C5 (GND), J2.SH, J3.1, J4.2 (Ext), J5.2 (Ext), J6.2, J7.1, J8.1, L1.1, Q2.2 (E), Q4.2 (E), Q7.2 (E), R7.2, R9.2, R10.2, R11.2, SW1.2, U1.57 (GND), U2.8 (GND), U2.13 (GND), U2.19 (GND), U2.21 (GND), U2.27 (GND), U2.30 (GND), U2.31 (GND), U2.33 (GND), U2.36 (GND), U2.37 (GND), U2.45 (GND), U2.63 (GND), U2.66 (GND), U2.67 (GND), U2.69 (GND), U2.70 (GND), U2.71 (GND), U2.72 (GND), U2.73 (GND), U2.74 (GND), U2.75 (GND), U2.76 (GND), U2.77 (GND), U3.5 (~ON/OFF), U3.6 (GND), U4.3, Y1.2, Y1.4
unnamed: AE1.1 (A), C1.1, L1.2
unnamed: BZ1.2 (-), Q4.3 (C)
unnamed: D1.2 (A), J1.A4 (VBUS), J1.A9 (VBUS), J1.B4 (VBUS), J1.B9 (VBUS)
unnamed: D4.1 (K), L2.1, U3.8 (OUT)
unnamed: J1.A5 (CC1), R11.1
unnamed: J1.B5 (CC2), R10.1
unnamed: J2.C3 (CLK), R12.2
unnamed: J2.C7 (I/O), R13.2
unnamed: J2.C2 (RST), R14.2
unnamed: C2.2, J4.1 (In), L3.1
unnamed: C19.2, J5.1 (In), L4.1
unnamed: Q1.1 (B), R5.2
unnamed: Q2.1 (B), R6.1
unnamed: Q3.1 (B), R4.2
unnamed: Q4.1 (B), R19.1
unnamed: Q5.1 (B), R21.2
unnamed: Q6.1 (B), R23.2
unnamed: Q7.1 (B), R15.2
unnamed: R16.2, U4.1
unnamed: R18.2, U5.1
unnamed: C3.1, R1.2, U1.4 (CHIP_PU/RESET)
unnamed: R9.1, U1.51 (GPIO45)
unnamed: R7.1, U1.52 (GPIO46)
unnamed: C1.2, U1.1 (LNA_IN/RF)
unnamed: C4.2, U1.53 (XTAL_N), Y1.3
unnamed: C5.2, U1.54 (XTAL_P), Y1.1
unnamed: TP1.1, U2.42 (STATUS)
VDD3P3: C9.1, FB1.1, U1.2 (VDD3P3), U1.3 (VDD3P3)

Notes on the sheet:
sim7080g
Power
USB-C
MCU <-> sim7080G
io1 io2 io4 -> mdb/rx io5 -> mdb/tx io6 -> pulse/rx io7 io8 -> dex/rx io9 -> dex/tx io10 -> i2c/sda io11 -> i2c/scl io12 -> buzzer io13 -> pulse/tx io14 -> sim7080g/pwrk io17 -> sim7080g/rx io18 -> sim7080g/tx io21 -> led
PULSE
DEX
i2c
VMC_

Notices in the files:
README.md:
License: MIT
